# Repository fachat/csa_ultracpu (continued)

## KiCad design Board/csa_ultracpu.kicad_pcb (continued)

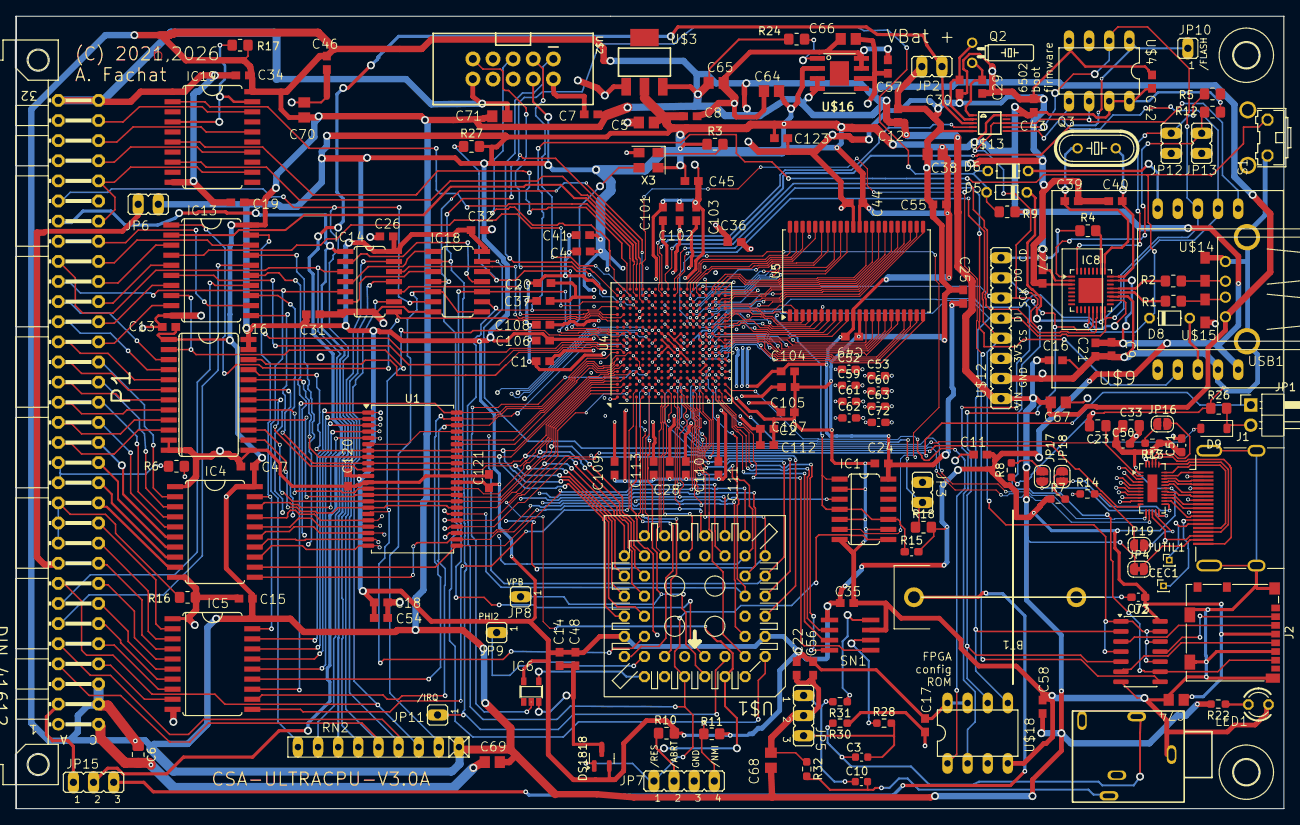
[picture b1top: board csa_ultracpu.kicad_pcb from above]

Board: 4 copper layers, 160.0 x 100.0 mm, 182 parts (0 on the bottom side), 253 nets.

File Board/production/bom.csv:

Designator,Footprint,Quantity,Value,LCSC Part #
"C1, C120, C123, C14, C4, C49, C54, C55, C56, C57, C9",C0603,11,1u,
"C10, C3",C050-025X075,2,1u,
"C101, C102, C103, C104, C105, C106, C107, C108, C109, C11, C110, C111, C112, C113, C12, C121, C13, C15, C16, C17, C18, C19, C2, C20, C21, C22, C24, C25, C26, C27, C28, C31, C32, C33, C34, C35, C36, C37, C41, C42, C43, C44, C45, C46, C47, C48, C58",C0603,47,0.1u,
"C29, C30, C39, C40",C0603,4,18p,
"C38, C5, C64, C65, C66, C67, C68, C69, C70, C71",C0805,10,22u,
C6,"E2,5-6",1,47u,
"C7, C8",C0603,2,100n,
"D1, D10, D2, D3, D4, D7",DO35-7,6,1N4148DO35-7,
"D5, D6, D8",D-5,3,1N4148,
D9,D-5,1,1N4448,
DS1818,TO92,1,DS1818,
"H3, H4","3,2",2,MOUNT-HOLE3.2,
"IC13, IC19",SO20W,2,74244DW,
IC14,SO14,1,74LVC14,
IC16,SO24L,1,74LVC8T245SO24,
IC18,SO14,1,74LVC06,
"IC2, IC4, IC5",SO20W,3,74HCT245DW,
IC3,SO14,1,74LVC125,
IC6,SOT23-5,1,741G04DBV,
IC7,SO16,1,74LVC138,
IC8,LQFP-32_5x5mm_P0.5mm,1,MAX3421E,
"JP1, JP12, JP13, JP2, JP3, JP4, JP6",JP1,7,JP1E,
"JP10, JP11, JP8, JP9",PIN,4,PIN,
JP5,JP2,1,JP2E,
JP7,JP4,1,JP4E,
LED1,LED3MM,1,LED3MM,
P1,CSABUS,1,CSABUS,
Q2,TC26H,1,32kHz,
Q3,HC49_S,1,12MHz,
"R1, R2, R4",0805,3,33,
"R10, R11, R12, R16, R17, R24, R25, R26, R27, R3, R5, R6, R9",0805,13,10k,
"R13, R14, R15",0204V,3,470,
"R18, R19, R20",0204V,3,1k,
R22,0207_2V,1,390,
"R28, R31",0204V,2,100,
R29,0207_2V,1,330,
"R30, R32",0204V,2,680,
"R7, R8",0204V,2,68,
RN2,RN-9,1,10k,
S1,B3F-31XX,1,31-XX,
SN1,SOIC8,1,MCP48X2,
U$1,PLCC44,1,W65C816SPLCC,
"U$10, U$11, U$14, U$15, U$5, U$6, U$8",SOD323,7,PESD5V0L1BA,
U$12,GRAVITECH-SDCARD,1,SD-CARD-GRAVI,
U$13,MSOP10,1,MCP79510,
U$16,PSOP-8-FIXED,1,AP2132B-1.2,
"U$18, U$4",DIL08,2,SPIFLASH,
U$2,TQFP144,1,XC6SLX9-TQG144,
U$3,SOT223,1,LDI1117,
U$7,FLAT10BOX,1,XILINXPROG,
U$9,ETHOLIENC,1,ETHOLIENC,
"U1, U2",TSOP-II-44_10.16x18.41mm_P0.8mm,2,IS61C5128AL-10TLI,
USB1,USB-A-H,1,USB-A-H,
X1,1503_09,1,SJ1-3513N,
X2,HDR15RA,1,D-SUB15-HDR15RA,
X3,Oscillator_SMD_SeikoEpson_SG8002CE-4Pin_3.2x2.5mm,1,SG-8002CE,

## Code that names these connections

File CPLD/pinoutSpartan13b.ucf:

#
# csa_ultracpu 1.3b
#
## NET VD<0>	LOC=P142 | IOSTANDARD=LVCMOS33 |PULLUP;
## NET VD<0>	LOC=P142 | IOSTANDARD=LVCMOS33 | DRIVE=16;

NET VD<0>	LOC=P47 | IOSTANDARD = LVTTL | TNM = "vd_tnm";	# RAMD0
NET VD<1>	LOC=P46 | IOSTANDARD = LVTTL | TNM = "vd_tnm";
NET VD<2>	LOC=P39 | IOSTANDARD = LVTTL | TNM = "vd_tnm";
NET VD<3>	LOC=P33 | IOSTANDARD = LVTTL | TNM = "vd_tnm";
NET VD<4>	LOC=P34 | IOSTANDARD = LVTTL | TNM = "vd_tnm";
NET VD<5>	LOC=P35 | IOSTANDARD = LVTTL | TNM = "vd_tnm";
NET VD<6>	LOC=P48 | IOSTANDARD = LVTTL | TNM = "vd_tnm";
NET VD<7>	LOC=P51 | IOSTANDARD = LVTTL | TNM = "vd_tnm";

NET VA<0>	LOC=P50 | IOSTANDARD = LVTTL;	# RAMA0
NET VA<1>	LOC=P55 | IOSTANDARD = LVTTL;
NET VA<2>	LOC=P58 | IOSTANDARD = LVTTL;
NET VA<3>	LOC=P60 | IOSTANDARD = LVTTL;	# RAMA3/M0
NET VA<4>	LOC=P61 | IOSTANDARD = LVTTL;
NET VA<5>	LOC=P66 | IOSTANDARD = LVTTL;	# RAMA5/VS1
NET VA<6>	LOC=P75 | IOSTANDARD = LVTTL;
NET VA<7>	LOC=P79 | IOSTANDARD = LVTTL;
NET VA<8>	LOC=P78 | IOSTANDARD = LVTTL;
NET VA<9>	LOC=P69 | IOSTANDARD = LVTTL;	# RAMA9/VS0
NET VA<10>	LOC=P57 | IOSTANDARD = LVTTL;
NET VA<11>	LOC=P62 | IOSTANDARD = LVTTL;	# RAMA11/VS2
NET VA<12>	LOC=P81 | IOSTANDARD = LVTTL;
NET VA<13>	LOC=P80 | IOSTANDARD = LVTTL;
NET VA<14>	LOC=P83 | IOSTANDARD = LVTTL;
NET VA<15>	LOC=P87 | IOSTANDARD = LVTTL;
NET VA<16>	LOC=P85 | IOSTANDARD = LVTTL;
NET VA<17>	LOC=P84 | IOSTANDARD = LVTTL;
NET VA<18>	LOC=P88 | IOSTANDARD = LVTTL;

NET FA<15>	LOC=P140 | IOSTANDARD = LVTTL;	# FA15
NET FA<16>	LOC=P141 | IOSTANDARD = LVTTL;
NET FA<17>	LOC=P143 | IOSTANDARD = LVTTL;
NET FA<18>	LOC=P144 | IOSTANDARD = LVTTL;	# FA18/HSWAP
NET FA<19>	LOC=P101 | IOSTANDARD = LVTTL;

NET D<0>	LOC=P2 | IOSTANDARD = LVTTL | TNM = "d_tnm";		# D0
NET D<1>	LOC=P1 | IOSTANDARD = LVTTL | TNM = "d_tnm";
NET D<2>	LOC=P14 | IOSTANDARD = LVTTL | TNM = "d_tnm";
NET D<3>	LOC=P5 | IOSTANDARD = LVTTL | TNM = "d_tnm";
NET D<4>	LOC=P12 | IOSTANDARD = LVTTL | TNM = "d_tnm";
NET D<5>	LOC=P8 | IOSTANDARD = LVTTL | TNM = "d_tnm";
NET D<6>	LOC=P9 | IOSTANDARD = LVTTL | TNM = "d_tnm";
NET D<7>	LOC=P6 | IOSTANDARD = LVTTL | TNM = "d_tnm";

NET A<0>	LOC=P17 | IOSTANDARD = LVTTL;	# A0
NET A<1>	LOC=P56 | IOSTANDARD = LVTTL;
NET A<2>	LOC=P45 | IOSTANDARD = LVTTL;
NET A<3>	LOC=P43 | IOSTANDARD = LVTTL;
NET A<4>	LOC=P44 | IOSTANDARD = LVTTL;
NET A<5>	LOC=P40 | IOSTANDARD = LVTTL;
NET A<6>	LOC=P41 | IOSTANDARD = LVTTL;
NET A<7>	LOC=P26 | IOSTANDARD = LVTTL;
NET A<8>	LOC=P30 | IOSTANDARD = LVTTL;
NET A<9>	LOC=P10 | IOSTANDARD = LVTTL;
NET A<10>	LOC=P11 | IOSTANDARD = LVTTL;
NET A<11>	LOC=P142 | IOSTANDARD = LVTTL;
NET A<12>	LOC=P127 | IOSTANDARD = LVTTL;
NET A<13>	LOC=P139 | IOSTANDARD = LVTTL;
NET A<14>	LOC=P119 | IOSTANDARD = LVTTL;
NET A<15>	LOC=P131 | IOSTANDARD = LVTTL;

NET VPA		LOC=P24 | IOSTANDARD = LVTTL;	# VPA
NET VDA		LOC=P22 | IOSTANDARD = LVTTL;	# VDA

NET NIOSEL	LOC=P134 | IOSTANDARD = LVTTL;	# /IOSEL

NET NVRAMSEL	LOC=P59 | IOSTANDARD = LVTTL;	# /RAMCS/M1
NET NFRAMSEL	LOC=P120 | IOSTANDARD = LVTTL;	# /FRAMSEL
NET RAMRWB	LOC=P82 | IOSTANDARD = LVTTL;	# /RAMWE

NET GRAPHIC	LOC=P137 | IOSTANDARD = LVTTL;	# GRAPHIC

NET HSYNC	LOC=P99 | IOSTANDARD = LVTTL;	# HSYNC
NET VSYNC	LOC=P98 | IOSTANDARD = LVTTL;	# VSYNC
NET PET_VSYNC	LOC=P92 | IOSTANDARD = LVTTL;	# PET_VSYNC

NET Q50M	LOC=P123 | IOSTANDARD = LVTTL;	# 50M
NET Q50M	BUFG=CLK;
NET Q50M 	PERIOD=20;

#NET DBG		LOC=P137 | IOSTANDARD = LVTTL;
NET RWB		LOC=P124 | IOSTANDARD = LVTTL;	#LOC=P134;	# R/-W
NET NRES	LOC=P117 | IOSTANDARD = LVTTL;	# /RES
NET NRES	BUFG=SR;

NET NIRQ 	LOC=P23 | IOSTANDARD = LVTTL;

#NET MLB		LOC=P21 | IOSTANDARD = LVTTL;
NET VPB			LOC=P7 | IOSTANDARD = LVTTL;
NET E			LOC=P21 | IOSTANDARD = LVTTL;
#NET MX			LOC=P24 | IOSTANDARD = LVTTL;

NET PHI2		LOC=P126 | IOSTANDARD = LVTTL;

NET RDY			LOC=P32 | IOSTANDARD = LVTTL;

NET EXTIO		LOC=P115 | IOSTANDARD = LVTTL;
NET IOINH		LOC=P111 | IOSTANDARD = LVTTL;
NET NMEMSEL		LOC=P112 | IOSTANDARD = LVTTL;
NET nbe_out		LOC=P132 | IOSTANDARD = LVTTL;	# /BE_OUT
NET nbe_dout		LOC=P133 | IOSTANDARD = LVTTL;	# /BE_DOUT
NET be_in		LOC=P118 | IOSTANDARD = LVTTL;
NET SYNC		LOC=P121 | IOSTANDARD = LVTTL;

NET CPHI2		LOC=P114 | IOSTANDARD = LVTTL;
NET C2PHI2		LOC=P104 | IOSTANDARD = LVTTL;
NET C8PHI2		LOC=P102 | IOSTANDARD = LVTTL;

NET PXL_OUT<0>		LOC=P93 | IOSTANDARD = LVTTL | PERIOD=40;	# IBOUT
NET PXL_OUT<1>		LOC=P94 | IOSTANDARD = LVTTL | PERIOD=40;	# BOUT
NET PXL_OUT<2>		LOC=P74 | IOSTANDARD = LVTTL | PERIOD=40;	# IGOUT
NET PXL_OUT<3>		LOC=P95 | IOSTANDARD = LVTTL | PERIOD=40;	# GOUT
NET PXL_OUT<4>		LOC=P105 | IOSTANDARD = LVTTL | PERIOD=40;	# IROUT
NET PXL_OUT<5>		LOC=P97 | IOSTANDARD = LVTTL | PERIOD=40;	# ROUT

NET SPI_SELA		LOC=P38 | IOSTANDARD = LVTTL;	# SPISELA/CSO_B
NET SPI_SELB		LOC=P29 | IOSTANDARD = LVTTL;
NET SPI_SELC		LOC=P27 | IOSTANDARD = LVTTL;

NET SPI_OUT		LOC=P64 | IOSTANDARD = LVTTL;	# SPI_MOSI
NET SPI_CLK		LOC=P100 | IOSTANDARD = LVTTL;	# SPI_CLK/CCLK
NET SPI_IN1		LOC=P65 | IOSTANDARD = LVTTL; # | PULLUP;	# SPI_MISO/DIN

NET SPI_IN3		LOC=P67 | IOSTANDARD = LVTTL | PULLUP;

NET SPI_NAUDIO		LOC=P116 | IOSTANDARD = LVTTL;
NET SPI_ACLK		LOC=P16 | IOSTANDARD = LVTTL;
NET SPI_AMOSI		LOC=P15 | IOSTANDARD = LVTTL;
NET NLDAC		LOC=P138 | IOSTANDARD = LVTTL;

#NET INIT_B		LOC=P | IOSTANDARD = LVTTL;

INST "NFRAMSEL"					TNM = "ram_tnm";
INST "NVRAMSEL"					TNM = "ram_tnm";
INST "RAMRWB"						TNM = "ram_tnm";

INST "SPI_CLK"						BUFG=CLK | TNM = "dotclk_tnm";
#INST "clocky/memclk_int"		BUFG=CLK;
INST "clocky/dotclk_int_1"		BUFG=CLK | TNM = "dotclk_tnm";
INST "q50m"							TNM = "qclk_tnm";
#INST "viccy/vid_fetch"			BUFG=CLK | TNM = "vidfetch_tnm";
TIMESPEC "ts_dotclk" = FROM "qclk_tnm" TO "dotclk_tnm" 3 ns DATAPATHONLY;
#TIMESPEC "ts_vidfetch" = FROM "qclk_tnm" to "vidfetch_tnm" 3 ns DATAPATHONLY;
TIMESPEC "ts_ram" = FROM "qclk_tnm" TO "ram_tnm" 4 ns DATAPATHONLY;

TIMESPEC "ts_vwrite"	= FROM "d_tnm" to "vd_tnm" 7 ns DATAPATHONLY;

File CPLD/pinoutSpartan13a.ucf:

#
## NET VD<0>	LOC=P142 | IOSTANDARD=LVCMOS33 |PULLUP;
## NET VD<0>	LOC=P142 | IOSTANDARD=LVCMOS33 | DRIVE=16;

NET VD<0>	LOC=P83;
NET VD<1>	LOC=P77;
NET VD<2>	LOC=P75;
NET VD<3>	LOC=P74;
NET VD<4>	LOC=P76;
NET VD<5>	LOC=P81;
NET VD<6>	LOC=P23;
NET VD<7>	LOC=P25;

NET VA<0>	LOC=P82;
NET VA<1>	LOC=P85;
NET VA<2>	LOC=P86;
NET VA<3>	LOC=P88;
NET VA<4>	LOC=P92;
NET VA<5>	LOC=P94;
NET VA<6>	LOC=P97;
NET VA<7>	LOC=P98;
NET VA<8>	LOC=P105;
NET VA<9>	LOC=P96;
NET VA<10>	LOC=P87;
NET VA<11>	LOC=P93;
NET VA<12>	LOC=P104;
NET VA<13>	LOC=P103;
NET VA<14>	LOC=P123;
NET VA<15>	LOC=P122;
NET VA<16>	LOC=P106;
NET VA<17>	LOC=P117;
NET VA<18>	LOC=P125;

NET FA<15>	LOC=P34;
NET FA<16>	LOC=P70;
NET FA<17>	LOC=P113;	#P71;
NET FA<18>	LOC=P53;
NET FA<19>	LOC=P142;

NET D<0>	LOC=P52;
NET D<1>	LOC=P51;
NET D<2>	LOC=P50;
NET D<3>	LOC=P3;	#P44;
NET D<4>	LOC=P43;
NET D<5>	LOC=P40;
NET D<6>	LOC=P26;	#P39;
NET D<7>	LOC=P35;

NET A<0>	LOC=P69;
NET A<1>	LOC=P68;
NET A<2>	LOC=P67;
NET A<3>	LOC=P66;
NET A<4>	LOC=P101;	#P63;
NET A<5>	LOC=P95;	#62;	#95;
NET A<6>	LOC=P120;	#P60;
NET A<7>	LOC=P59;
NET A<8>	LOC=P58;
NET A<9>	LOC=P111;	#P57;
NET A<10>	LOC=P56;
NET A<11>	LOC=P31;
NET A<12>	LOC=P48;
NET A<13>	LOC=P47;
NET A<14>	LOC=P41;
NET A<15>	LOC=P38;

NET VPA		LOC=P29;
NET VDA		LOC=P6;

NET NIOSEL	LOC=P33;

NET NVRAMSEL	LOC=P91;
NET NFRAMSEL	LOC=P112;
NET RAMRWB	LOC=P8;

NET GRAPHIC	LOC=P36;

NET HSYNC	LOC=P15;
NET VSYNC	LOC=P16;
NET PET_VSYNC	LOC=P7;

NET Q50M	LOC=P128;
NET Q50M	BUFG=CLK;
NET Q50M PERIOD=20;

NET RWB		LOC=P129;
NET NRES	LOC=P107;
NET NRES	BUFG=SR;

NET PHI2_IO	LOC=P116;	# UNUSED!!!
NET PHI2_IO	BUFG=CLK;

##NET MLB		LOC=P21;
##NET VPB		LOC=P22;
NET E			LOC=P141;
##NET MX			LOC=P24;

NET SPI_IN3		LOC=P78;

NET NFLASH		LOC=P21;
NET SPI_NSEL2		LOC=P143;
#NET SPI_NSEL3		LOC=P3;
NET SPI_NSEL4		LOC=P4;

#NET SPI_NSEL5		LOC=P26;

##NET MEMCLK		BUFG=CLK;
##NET MEMCLK		NOREDUCE;
#
##NET PHI2		BUFG=CLK;
NET PHI2		LOC=P2;

NET RDY			LOC=P136;

NET EXTIO		LOC=P12;
NET IOINH		LOC=P10;
NET NMEMSEL		LOC=P132;
NET nbe_out		LOC=P32;
NET nbe_dout		LOC=P139;
NET be_in		LOC=P18;
NET SYNC		LOC=P135;

NET CPHI2		LOC=P134;
NET C2PHI2		LOC=P130;
NET C8PHI2		LOC=P131;

#NET COLORLD		LOC=P54;
#NET COLORLD2		LOC=P16;

#NET DENA	LOC=P5;
#NET PXLLD		LOC=P126;
#NET NSRLOAD		LOC=P14;
#NET nchromaddr		LOC=P140;
#NET DCLK	LOC=P20;	# SRCLK

NET PXL_OUT<0>	LOC=P14;	# ROUT IOUT
NET PXL_OUT<1>	LOC=P126;# GOUT BOUT
NET PXL_OUT<3>	LOC=P20;	# BOUT ROUT
NET PXL_OUT<2>	LOC=P140;# IOUT GOUT
#
#NET SPI_OUT		LOC=P44;	#P22;
#NET SPI_CLK		LOC=P71;	#P17;
#NET NFLASH		LOC=P39;	#P21;
#NET SPI_IN1		LOC=P63;	#P89;

NET SPI_OUT		LOC=P22;
NET SPI_CLK		LOC=P17;
NET NFLASH		LOC=P21;
NET SPI_IN1		LOC=P89;

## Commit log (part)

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2022-04-23 update README, add pictures
2022-04-23 updated readmes
2022-04-23 Trying to fix a strange non-reset on power-up behaviour
2022-04-23 clean up README: remove 8x96 mapping, hires; update boot menu
2022-04-24 VHDL cleanup of unused signals
2022-04-24 shrink image file size
2022-05-14 sync 1Mhz bus and CPU trigger; re-enable 8296
2022-05-15 update ROM
2022-05-15 add benchmark code
2022-05-15 adapt tests for the Ultra-PET
2023-03-25 updated pinout to compile for Spartan
2023-07-19 GRAPHICS now goes to a level shifting inverter
2023-07-19 obsolete IC7 by storing character index in the FPGA
2023-07-20 deprecating IC9, IC11 on ultracpu 1.2b by moving stuff into the FPGA
2023-07-23 obsolete IC12, IC15 by pulling into FPGA
2023-07-23 cleanup code
2023-07-23 more cleanup
2023-07-23 work on a timing issue between pixel output and hsync;
2023-07-25 cleanup, make video interface simpler
2023-08-01 move I/O around to free FPGA bot prom lines
2023-08-07 change layout, add bin and mcs FPGA images, and mkbin.sh script
2023-08-11 new pinout for ucpu 1.3b
2023-08-11 added signals to ucpu pinout
2023-08-11 pinout for 1.3b
2023-08-11 re-route vpb
2023-08-14 started working on requirements for Viccy-II
2023-08-15 work on Viccy II reqs2
2023-08-15 working on Viccy-II
2023-08-15 work on Viccy-II
2023-08-15 more work on Viccy-II - broken
2023-08-16 work on Viccy attribute timing
2023-08-24 more work on pixel pipeline
2023-08-24 fixed pixel timing!
2023-08-25 introduce separate attr and crom pointers as Viccy registers
2023-09-01 work on reading the registers, and auto-increase index
2023-09-02 introduce VGA Canvas
2023-09-10 work on h border timing
2023-09-10 stabillilize border
2023-09-23 more work on ground up timing rework
2023-09-23 more work on h timing
2023-09-24 horizontal timing complete w/ r1,r25.4,r44
2023-09-25 add upet compat mode, disp enable
2023-09-25 first refactor of vertical timing/border
2023-09-26 cleanup; move interlace/double/80 to r8; vert timing
2023-09-26 vshift almost working
2023-09-26 vertical timing, incl. v_shift
2023-09-26 implemented h_shift
2023-09-26 implement address offset r27
2023-09-26 fix hires address calculation
2023-09-26 started working on raster interrupt - but current test hw has no irq output...
2023-09-27 works with ultracpu 1.3b
2023-09-27 small fixes/reverts
2023-09-27 compare regs with VDC from https://www.c64-wiki.de/wiki/VDC, add TODOs
2023-09-28 small fixes, first demo
2023-10-01 working on the demo
2023-10-01 fixed some init bugs, reverse r24 shift
2023-10-07 make attr. colour shift w/ horizontal smooth scroll
2023-10-07 alternatve video address works
2023-10-15 mapper simplification
2023-10-15 change top clock to q50m/dotclk instead of memclk
2023-10-15 switch timing to q50m in ipl
2023-10-15 fix vborder / vtiming
2023-10-16 Fix vertical border timing
2023-10-16 timing...
2023-10-16 pin constraints to LVTTL
2023-10-17 clarify vramrwb - now half qclk behind select
2023-10-17 cleanup video code
2023-10-17 add Init_b to pinout desc
2023-10-17 fix number of written viccy registers in demo (was triggering alt address)
2023-10-17 more work on vborder
2023-10-17 fix blinking
2023-10-18 simplify clocky, add maxskew constraint
2023-10-18 simplify top; add system jitter attribute on qclk
2023-10-18 fetch attrib only when needed
2023-10-18 add from-to time constraint in ucf
2023-10-19 make vert scroll and changing charsets work
2023-10-19 double possible # of char lines; fix border bug in smooth horizontal scroll
2023-10-19 add maxdelay constraint to dotclk
2023-10-19 fix resetable address counters, add resetable rc counter
2023-10-19 adapt to r46
2023-10-21 prep demo for resetable counters
2023-10-21 upet compat for vid addr; move rasterline counter to r30/31
2023-10-21 add hires demo
2023-10-21 fix one-off starting border in 40col mode
2023-10-21 start on multicolour
2023-10-21 multicolour mode working
2023-10-22 first sprite (display only, no read yet)
2023-10-22 sprite colours
2023-10-23 work on sprites
2023-10-23 more work on sprites
2023-10-24 more work on sprites, expand, reg access, data fetch
2023-10-24 more work on sprites; over/under raster, over/under border
2023-10-24 vertical raster / border timing
2023-10-24 sprite y
2023-10-25 sprite multicolur
2023-10-25 move sprite fetch out of raster's way
2023-10-25 8 sprites; fix sprite fetch; fine coordinate mode
2023-10-25 add demos; adjust sprite bitmap to c64 format; on border bit does not affect on raster
2023-10-25 add FPGA config flash image
2023-10-25 fine tune sprite limits
2023-10-29 update demos
2023-11-02 video clean, start working on DAC
2023-11-02 Ethernet test code
2023-11-02 integrate DAC fetch
2023-11-02 small optimization in mapper
2023-11-02 more work on DAC integration
2023-11-03 more work on dac
2023-11-03 basic dma engine to send out data via dac
2023-11-04 DMA engine for DAC working
2023-11-05 work on DAC
2023-11-05 cleanup dac, update test
2023-11-05 FPGA config ROM, addl. test
2023-11-05 make DAC DMA len full VRAM size
2023-11-06 dac dma interrupt
2023-11-06 work on DAC DMA IRQ and restart
2023-11-08 FPGA flash image
2023-11-08 DAC documentation
2023-11-08 implement memory-mapped viccy register option
2023-11-09 implement Viccy R22 & R23
2023-11-09 refactor hshift, work on collisions
2023-11-11 sprite-border collision
2023-11-11 sprite-raster and sprite-sprite collisions
2023-11-11 add R22/R23 effects to demo
2023-11-11 implemented - not tested yet - sprite/border/raster/sprite interrupts
2023-11-12 refactored sprite handling into own file
2023-11-12 add note on refactoring
2023-11-12 fix missing sprite-border interrupt
2023-11-26 re-org of Viccy registers
2023-11-26 option to use xxx as window to CS/A bus IO area
2023-11-26 enable read out of Micro-PET control registers
2023-11-27 update FPGA config ROM
2023-12-11 update doc about Viccy registers
2023-12-11 shorten bus phi2 a bit on write cycles, to allow for better hold times; required by CSA_NETUSB it seems
2023-12-12 newer images
2023-12-12 update Video description
2023-12-12 link DAC description in README
2023-12-12 editor updates
2023-12-14 update ipl code to colour-boot again
2023-12-14 fix x/y swap in 40 col extended editor
2023-12-14 refactor boot code further out
2023-12-17 fix autostart bug introduced in last patch
2023-12-17 make USB keyboard scan during boot screen - but not used yet
2023-12-17 experimental support for USB keyboards on BASIC4
2023-12-20 update usb code to handle Ctrl-C
2023-12-21 separate out video map into own control register
2023-12-21 avoid reading MAPREG (upet compat)
2023-12-21 revert to VDRIVE interrupt on boot (upet compat)
2023-12-21 add name/copyright on boot screen
2023-12-29 make keyboard scan work even in absence of USB
2024-01-04 update memory map in README
2024-02-03 implement dual mono for DAC
2024-02-03 update DAC docs
2024-02-03 updated some constraints, video timing for 70Mhz - but not working
2024-02-05 initial dry-run spartan6
2024-02-06 implement palette in viccy-ii for 2/2/2 RGB
2024-02-09 add palette support
2024-02-09 add alternate palette support
2024-02-09 new fpga config prom image
2024-02-12 re-factor FPGA code such that it can more easily be reused in other systems
2024-02-12 cleanup
2024-03-22 first work
2024-03-22 work
2024-03-24 more work
2024-03-24 more work - boots, bleeds bank0 writes into vram
2024-03-25 vram timing ok; init issues (boot to 8032 before fpga load); ieee irq issues still; leftmost pixel error
2024-03-25 incremental
2024-03-25 stable timing, but no CPU reaction
2024-03-25 fix ipl write; delay cpu phi2 to stabilize timing
2024-03-25 back to 50m
2024-03-26 registering A in mapper works at 50m
2024-03-26 more clock phases
2024-03-26 working with 12MHz
2024-03-26 ok 12M; improve timing
2024-03-27 first light on 70Mhz
2024-03-27 even runs at 17MHz...- going into FPGA placement territory it seems
2024-03-27 still ok but better scope trigger
2024-03-27 add time constraint for VRAM write
2024-03-27 update center position; update ROM
2024-03-27 make vertical offset work
2024-03-28 fix LDAC back to original
2024-03-29 SPI changes
2024-03-29 improve docs, fix virtpet
2024-03-29 make sure SD cards work by adding pullup to SD-Card specfici MISO signal
2024-04-21 pinout 1.4a /ulti 1.0a; 1mhz cpu clk timing
2024-04-21 fix bus timing
2024-04-25 IPL waits a time before using spi_clk as the FPGA seems to switch if off way after initial config is done...
2024-04-29 fix R25 bitwise shift logic
2024-04-29 fix vertical position; sprite fetch
2024-04-29 update boot ROM, updemo
2024-04-29 update updemo; try to fix left border start in 40 col mode (8 pix too late)
2024-04-30 fix 40 col left border start
2024-04-30 add missing boot rom src files, new images
2024-05-05 add uPet CPLD shell
2024-05-06 add binary rom image for FPGA
2024-05-23 fix upet shell for non-inverted graphics input; dacfile for new clock speed
2024-05-24 add shell for UltraCPU / UltiPET
2024-06-17 separate out ROM, CPLD/FPGA, update readme
2024-06-17 update board to 2.0b from internal repo
2024-06-19 add missing images
2024-06-20 add link to family repo
2024-06-26 handle (no) sub repos
2024-12-13 more work on r2.1a
2024-12-15 more work on r2.1a - only bom xls is missing/outdated
2024-12-25 add Flash ROM type prints on PCB
2024-12-26 first try on BOM
2024-12-26 ultracpu 2.1a
2024-12-28 work on BOM
2024-12-31 fix bom
2025-01-17 r2.1a-fixes
2026-06-02 start r2.2a, moving from VGA to HDMI
